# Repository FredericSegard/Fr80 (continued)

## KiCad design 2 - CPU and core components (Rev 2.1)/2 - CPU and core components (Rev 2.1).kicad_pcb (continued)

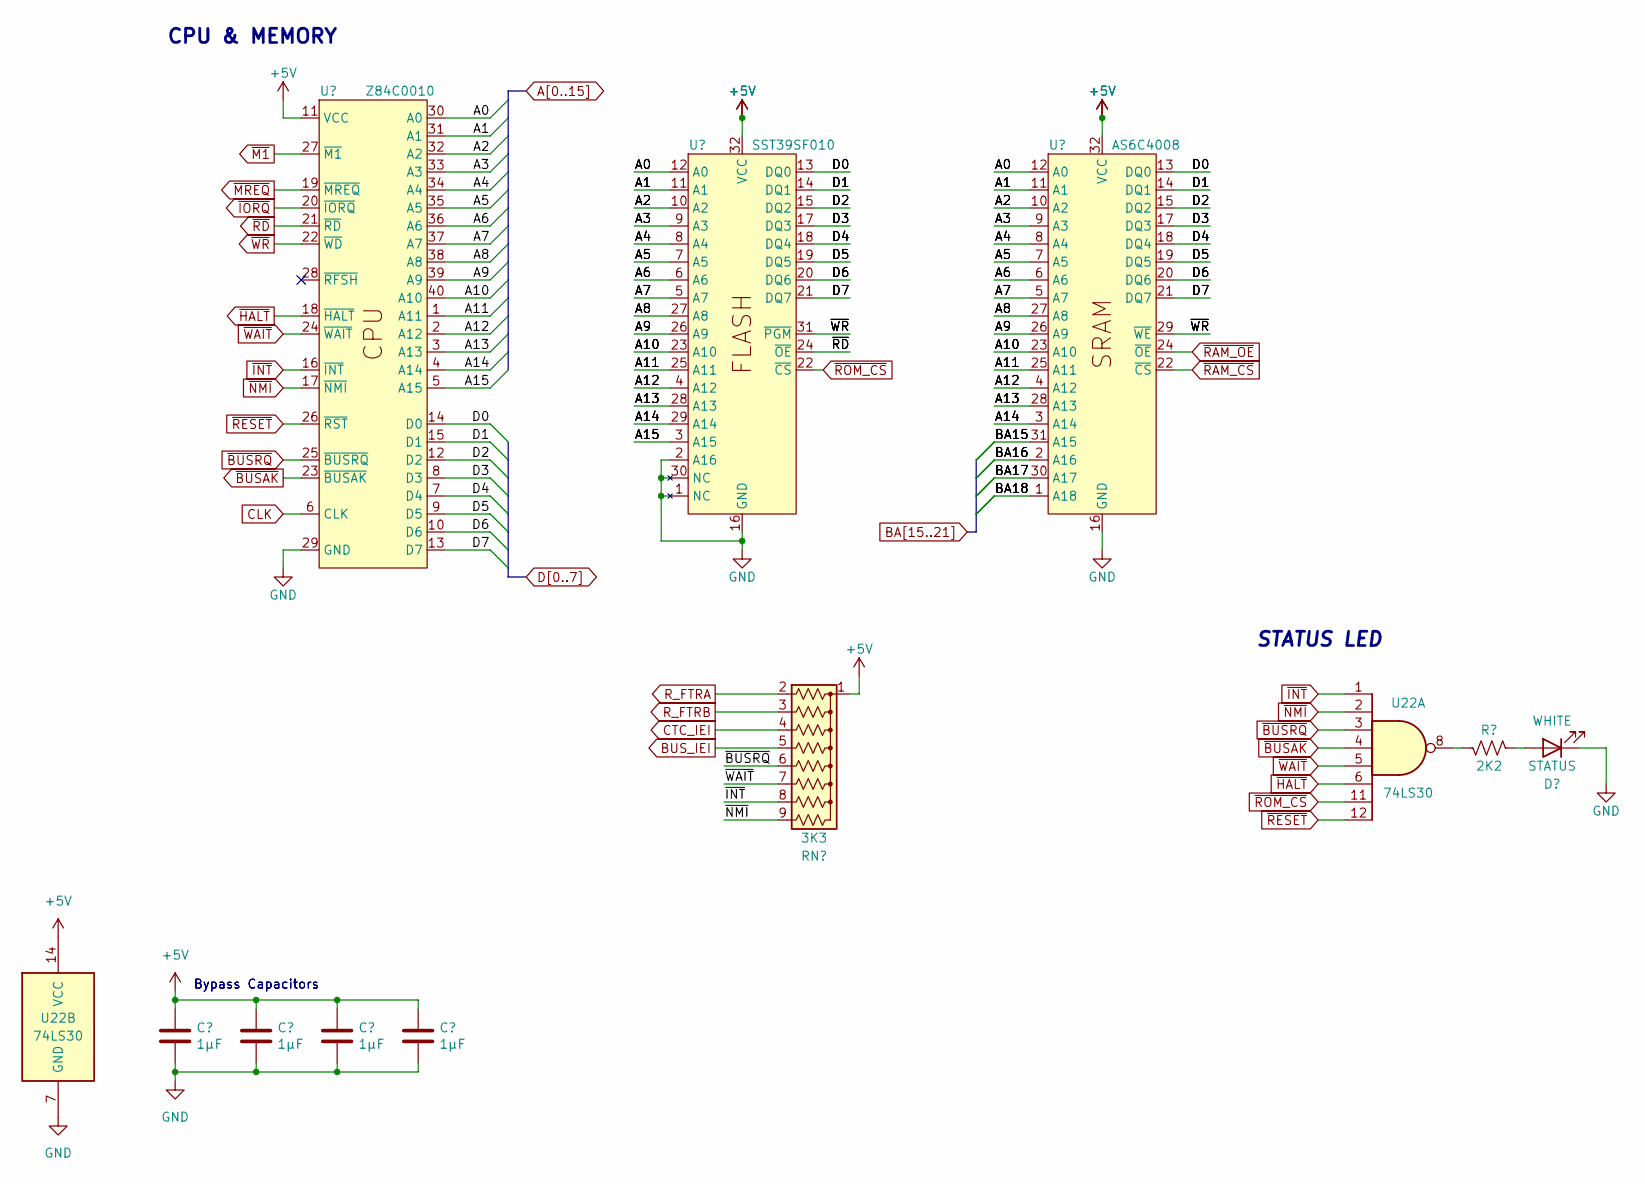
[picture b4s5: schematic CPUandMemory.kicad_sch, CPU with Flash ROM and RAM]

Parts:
C17, C18, C19, C26: 1µF; C_Disc_D3.4mm_W2.1mm_P2.50mm
D1: STATUS; LED_D3.0mm_Horizontal_O1.27mm_Z2.0mm_Clear
R2: 2K2; R_Axial_DIN0207_L6.3mm_D2.5mm_P10.16mm_Horizontal
RN3: 3K3; R_Array_SIP9
U15: Z84C0010; DIP-40_W15.24mm_Socket
U16: SST39SF010; ZIF_Socket-32
U17: AS6C4008; DIP-32_W15.24mm_Socket
U22: 74LS30; DIP-14_W7.62mm_Socket

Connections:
A0: U15.30 (A0), U16.12 (A0), U17.12 (A0); also elsewhere on the board
A1: U15.31 (A1), U16.11 (A1), U17.11 (A1); also elsewhere on the board
A2: U15.32 (A2), U16.10 (A2), U17.10 (A2); also elsewhere on the board
A3: U15.33 (A3), U16.9 (A3), U17.9 (A3); also elsewhere on the board
A4: U15.34 (A4), U16.8 (A4), U17.8 (A4); also elsewhere on the board
A5: U15.35 (A5), U16.7 (A5), U17.7 (A5); also elsewhere on the board
A6: U15.36 (A6), U16.6 (A6), U17.6 (A6); also elsewhere on the board
A7: U15.37 (A7), U16.5 (A7), U17.5 (A7); also elsewhere on the board
A8: U15.38 (A8), U16.27 (A8), U17.27 (A8); also elsewhere on the board
A9: U15.39 (A9), U16.26 (A9), U17.26 (A9); also elsewhere on the board
A10: U15.40 (A10), U16.23 (A10), U17.23 (A10); also elsewhere on the board
A11: U15.1 (A11), U16.25 (A11), U17.25 (A11); also elsewhere on the board
A12: U15.2 (A12), U16.4 (A12), U17.4 (A12); also elsewhere on the board
A13: U15.3 (A13), U16.28 (A13), U17.28 (A13); also elsewhere on the board
A14: U15.4 (A14), U16.29 (A14), U17.3 (A14); also elsewhere on the board
A15: U15.5 (A15), U16.3 (A15); also elsewhere on the board
BA15: U17.31 (A15); also elsewhere on the board
BA16: U17.2 (A16); also elsewhere on the board
BA17: U17.30 (A17); also elsewhere on the board
BA18: U17.1 (A18); also elsewhere on the board
BUS_IEI: RN3.5 (R4); also elsewhere on the board
CLK: U15.6 (CLK); also elsewhere on the board
CTC_IEI: RN3.4 (R3); also elsewhere on the board
D0: U15.14 (D0), U16.13 (DQ0), U17.13 (DQ0); also elsewhere on the board
D1: U15.15 (D1), U16.14 (DQ1), U17.14 (DQ1); also elsewhere on the board
D2: U15.12 (D2), U16.15 (DQ2), U17.15 (DQ2); also elsewhere on the board
D3: U15.8 (D3), U16.17 (DQ3), U17.17 (DQ3); also elsewhere on the board
D4: U15.7 (D4), U16.18 (DQ4), U17.18 (DQ4); also elsewhere on the board
D5: U15.9 (D5), U16.19 (DQ5), U17.19 (DQ5); also elsewhere on the board
D6: U15.10 (D6), U16.20 (DQ6), U17.20 (DQ6); also elsewhere on the board
D7: U15.13 (D7), U16.21 (DQ7), U17.21 (DQ7); also elsewhere on the board
R_FTRB: RN3.3 (R2); also elsewhere on the board
~BUSAK: U15.23 (~BUSAK), U22.4; also elsewhere on the board
~BUSRQ: RN3.6 (R5), U15.25 (~BUSRQ), U22.3; also elsewhere on the board
~HALT: U15.18 (~HALT), U22.6; also elsewhere on the board
~INT: RN3.8 (R7), U15.16 (~INT), U22.1; also elsewhere on the board
~IORQ: U15.20 (~IORQ); also elsewhere on the board
~M1: U15.27 (~M1); also elsewhere on the board
~MREQ: U15.19 (~MREQ); also elsewhere on the board
~NMI: RN3.9 (R8), U15.17 (~NMI), U22.2; also elsewhere on the board
~RAM_CS: U17.22 (~CS); also elsewhere on the board
~RAM_OE: U17.24 (~OE); also elsewhere on the board
~RD: U15.21 (~RD), U16.24 (~OE); also elsewhere on the board
~RESET: U15.26 (~RST), U22.12; also elsewhere on the board
~ROM_CS: U16.22 (~CS), U22.11; also elsewhere on the board
~WAIT: RN3.7 (R6), U15.24 (~WAIT), U22.5; also elsewhere on the board
~WR: U15.22 (~WD), U16.31 (~PGM), U17.29 (~WE); also elsewhere on the board

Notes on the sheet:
STATUS LED
Bypass Capacitors
CPU & MEMORY

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
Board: 2 copper layers, 75 parts (0 on the bottom side), 163 nets, no tracks yet.

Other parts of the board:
D9: STATUS; LED_D3.0mm_Horizontal_O1.27mm_Z2.0mm_Clear
R7: 2K2; R_Axial_DIN0207_L6.3mm_D2.5mm_P10.16mm_Horizontal

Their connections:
unnamed: D9.2 (A), R7.1

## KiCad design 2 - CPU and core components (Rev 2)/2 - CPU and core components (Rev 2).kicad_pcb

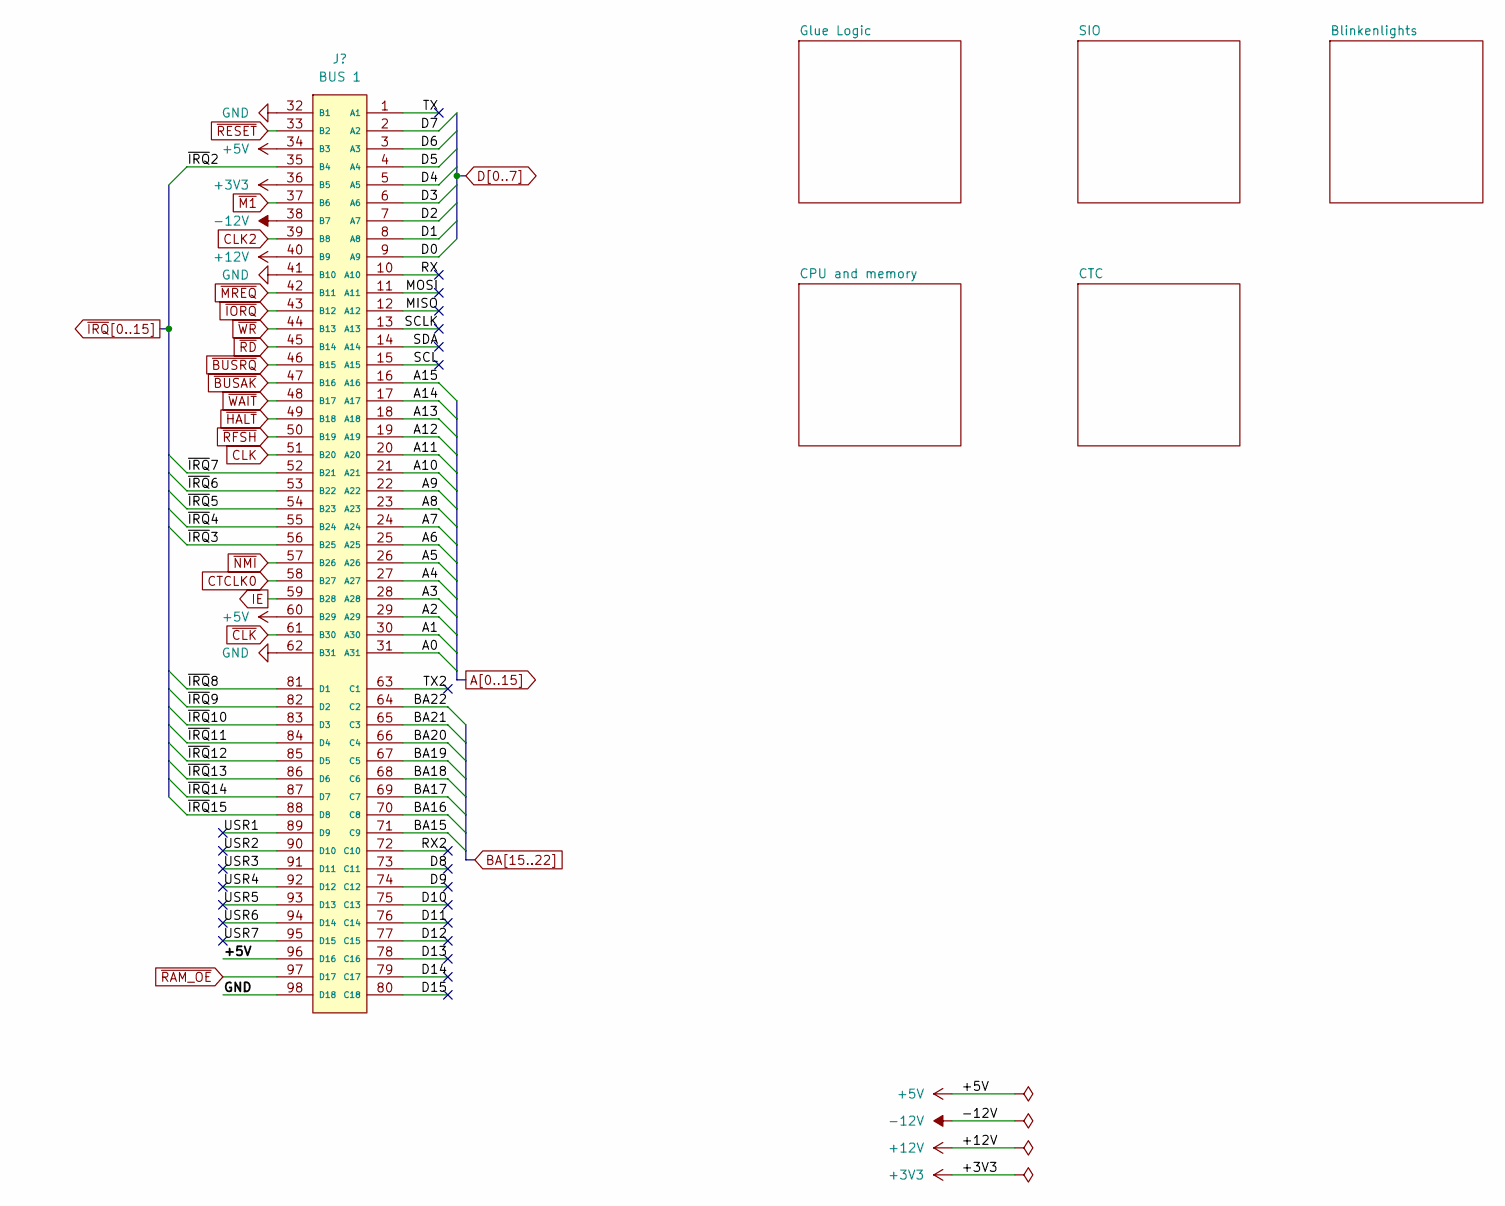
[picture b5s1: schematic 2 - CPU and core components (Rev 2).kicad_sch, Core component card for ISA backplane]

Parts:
J2: BUS 1; BUS_AT v2

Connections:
+3V3: J2.36 (B5)
+5V: J2.34 (B3), J2.60 (B29), J2.96 (D16); also elsewhere on the board
+12V: J2.40 (B9)
-12V: J2.38 (B7)
/D8: J2.73 (C11)
/D9: J2.74 (C12)
/D10: J2.75 (C13)
/D11: J2.76 (C14)
/D12: J2.77 (C15)
/D13: J2.78 (C16)
/D14: J2.79 (C17)
/D15: J2.80 (C18)
/MISO: J2.12 (A12)
/MOSI: J2.11 (A11)
/RX: J2.10 (A10)
/RX2: J2.72 (C10)
/SCL: J2.15 (A15)
/SCLK: J2.13 (A13)
/SDA: J2.14 (A14)
/TX: J2.1 (A1)
/TX2: J2.63 (C1)
/USR1: J2.89 (D9)
/USR2: J2.90 (D10)
/USR3: J2.91 (D11)
/USR4: J2.92 (D12)
/USR5: J2.93 (D13)
/USR6: J2.94 (D14)
/USR7: J2.95 (D15)
A0: J2.31 (A31); also elsewhere on the board
A1: J2.30 (A30); also elsewhere on the board
A2: J2.29 (A29); also elsewhere on the board
A3: J2.28 (A28); also elsewhere on the board
A4: J2.27 (A27); also elsewhere on the board
A5: J2.26 (A26); also elsewhere on the board
A6: J2.25 (A25); also elsewhere on the board
A7: J2.24 (A24); also elsewhere on the board
A8: J2.23 (A23); also elsewhere on the board
A9: J2.22 (A22); also elsewhere on the board
A10: J2.21 (A21); also elsewhere on the board
A11: J2.20 (A20); also elsewhere on the board
A12: J2.19 (A19); also elsewhere on the board
A13: J2.18 (A18); also elsewhere on the board
A14: J2.17 (A17); also elsewhere on the board
A15: J2.16 (A16); also elsewhere on the board
BA15: J2.71 (C9); also elsewhere on the board
BA16: J2.70 (C8); also elsewhere on the board
BA17: J2.69 (C7); also elsewhere on the board
BA18: J2.68 (C6); also elsewhere on the board
BA19: J2.67 (C5); also elsewhere on the board
BA20: J2.66 (C4); also elsewhere on the board
BA21: J2.65 (C3); also elsewhere on the board
BA22: J2.64 (C2); also elsewhere on the board
CLK: J2.51 (B20); also elsewhere on the board
CLK2: J2.39 (B8); also elsewhere on the board
CTCLK0: J2.58 (B27); also elsewhere on the board
D0: J2.9 (A9); also elsewhere on the board
D1: J2.8 (A8); also elsewhere on the board
D2: J2.7 (A7); also elsewhere on the board
D3: J2.6 (A6); also elsewhere on the board
D4: J2.5 (A5); also elsewhere on the board
D5: J2.4 (A4); also elsewhere on the board
D6: J2.3 (A3); also elsewhere on the board
D7: J2.2 (A2); also elsewhere on the board
GND: J2.32 (B1), J2.41 (B10), J2.62 (B31), J2.98 (D18); also elsewhere on the board
IE: J2.59 (B28); also elsewhere on the board
~BUSAK: J2.47 (B16); also elsewhere on the board
~BUSRQ: J2.46 (B15); also elsewhere on the board
~CLK: J2.61 (B30); also elsewhere on the board
~HALT: J2.49 (B18); also elsewhere on the board
~IORQ: J2.43 (B12); also elsewhere on the board
~IRQ2: J2.35 (B4); also elsewhere on the board
~IRQ3: J2.56 (B25); also elsewhere on the board
~IRQ4: J2.55 (B24); also elsewhere on the board
~IRQ5: J2.54 (B23); also elsewhere on the board
~IRQ6: J2.53 (B22); also elsewhere on the board
~IRQ7: J2.52 (B21); also elsewhere on the board
~IRQ8: J2.81 (D1); also elsewhere on the board
~IRQ9: J2.82 (D2); also elsewhere on the board
~IRQ10: J2.83 (D3); also elsewhere on the board
~IRQ11: J2.84 (D4); also elsewhere on the board
~IRQ12: J2.85 (D5); also elsewhere on the board
~IRQ13: J2.86 (D6); also elsewhere on the board
~IRQ14: J2.87 (D7); also elsewhere on the board
~IRQ15: J2.88 (D8); also elsewhere on the board
~M1: J2.37 (B6); also elsewhere on the board
~MREQ: J2.42 (B11); also elsewhere on the board
~NMI: J2.57 (B26); also elsewhere on the board
~RAM_OE: J2.97 (D17); also elsewhere on the board
~RD: J2.45 (B14); also elsewhere on the board
~RESET: J2.33 (B2); also elsewhere on the board
~RFSH: J2.50 (B19); also elsewhere on the board
~WAIT: J2.48 (B17); also elsewhere on the board
~WR: J2.44 (B13); also elsewhere on the board

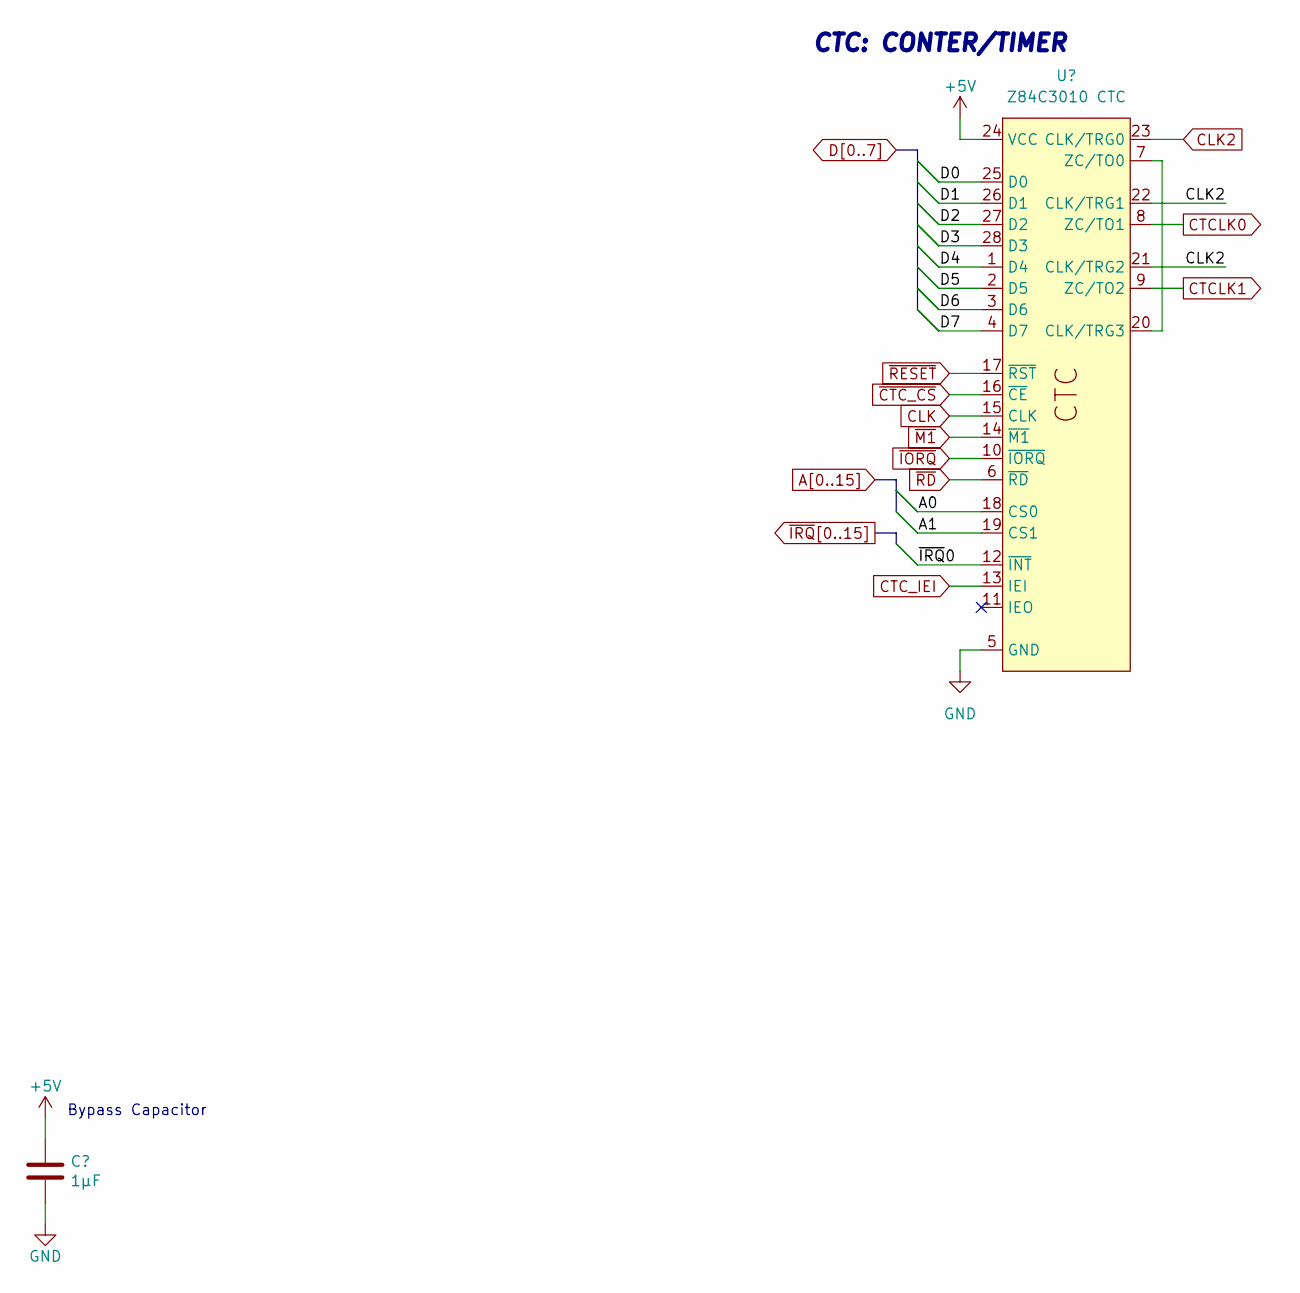
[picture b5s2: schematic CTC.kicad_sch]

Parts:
C14: 1µF; C_Disc_D3.4mm_W2.1mm_P2.50mm
U13: Z84C3010 CTC; DIP-28_W15.24mm_Socket

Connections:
+5V: C14.1, U13.24 (VCC); also elsewhere on the board
A0: U13.18 (CS0); also elsewhere on the board
A1: U13.19 (CS1); also elsewhere on the board
CLK: U13.15 (CLK); also elsewhere on the board
CLK2: U13.21 (CLK/TRG2), U13.22 (CLK/TRG1), U13.23 (CLK/TRG0); also elsewhere on the board
CTCLK0: U13.8 (ZC/TO1); also elsewhere on the board
CTCLK1: U13.9 (ZC/TO2); also elsewhere on the board
CTC_IEI: U13.13 (IEI); also elsewhere on the board
D0: U13.25 (D0); also elsewhere on the board
D1: U13.26 (D1); also elsewhere on the board
D2: U13.27 (D2); also elsewhere on the board
D3: U13.28 (D3); also elsewhere on the board
D4: U13.1 (D4); also elsewhere on the board
D5: U13.2 (D5); also elsewhere on the board
D6: U13.3 (D6); also elsewhere on the board
D7: U13.4 (D7); also elsewhere on the board
GND: C14.2, U13.5 (GND); also elsewhere on the board
unnamed: U13.7 (ZC/TO0), U13.20 (CLK/TRG3)
~CTC_CS: U13.16 (~CE); also elsewhere on the board
~IORQ: U13.10 (~IORQ); also elsewhere on the board
~IRQ0: U13.12 (~INT); also elsewhere on the board
~M1: U13.14 (~M1); also elsewhere on the board
~RD: U13.6 (~RD); also elsewhere on the board
~RESET: U13.17 (~RST); also elsewhere on the board

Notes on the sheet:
CTC: CONTER/TIMER
Bypass Capacitor

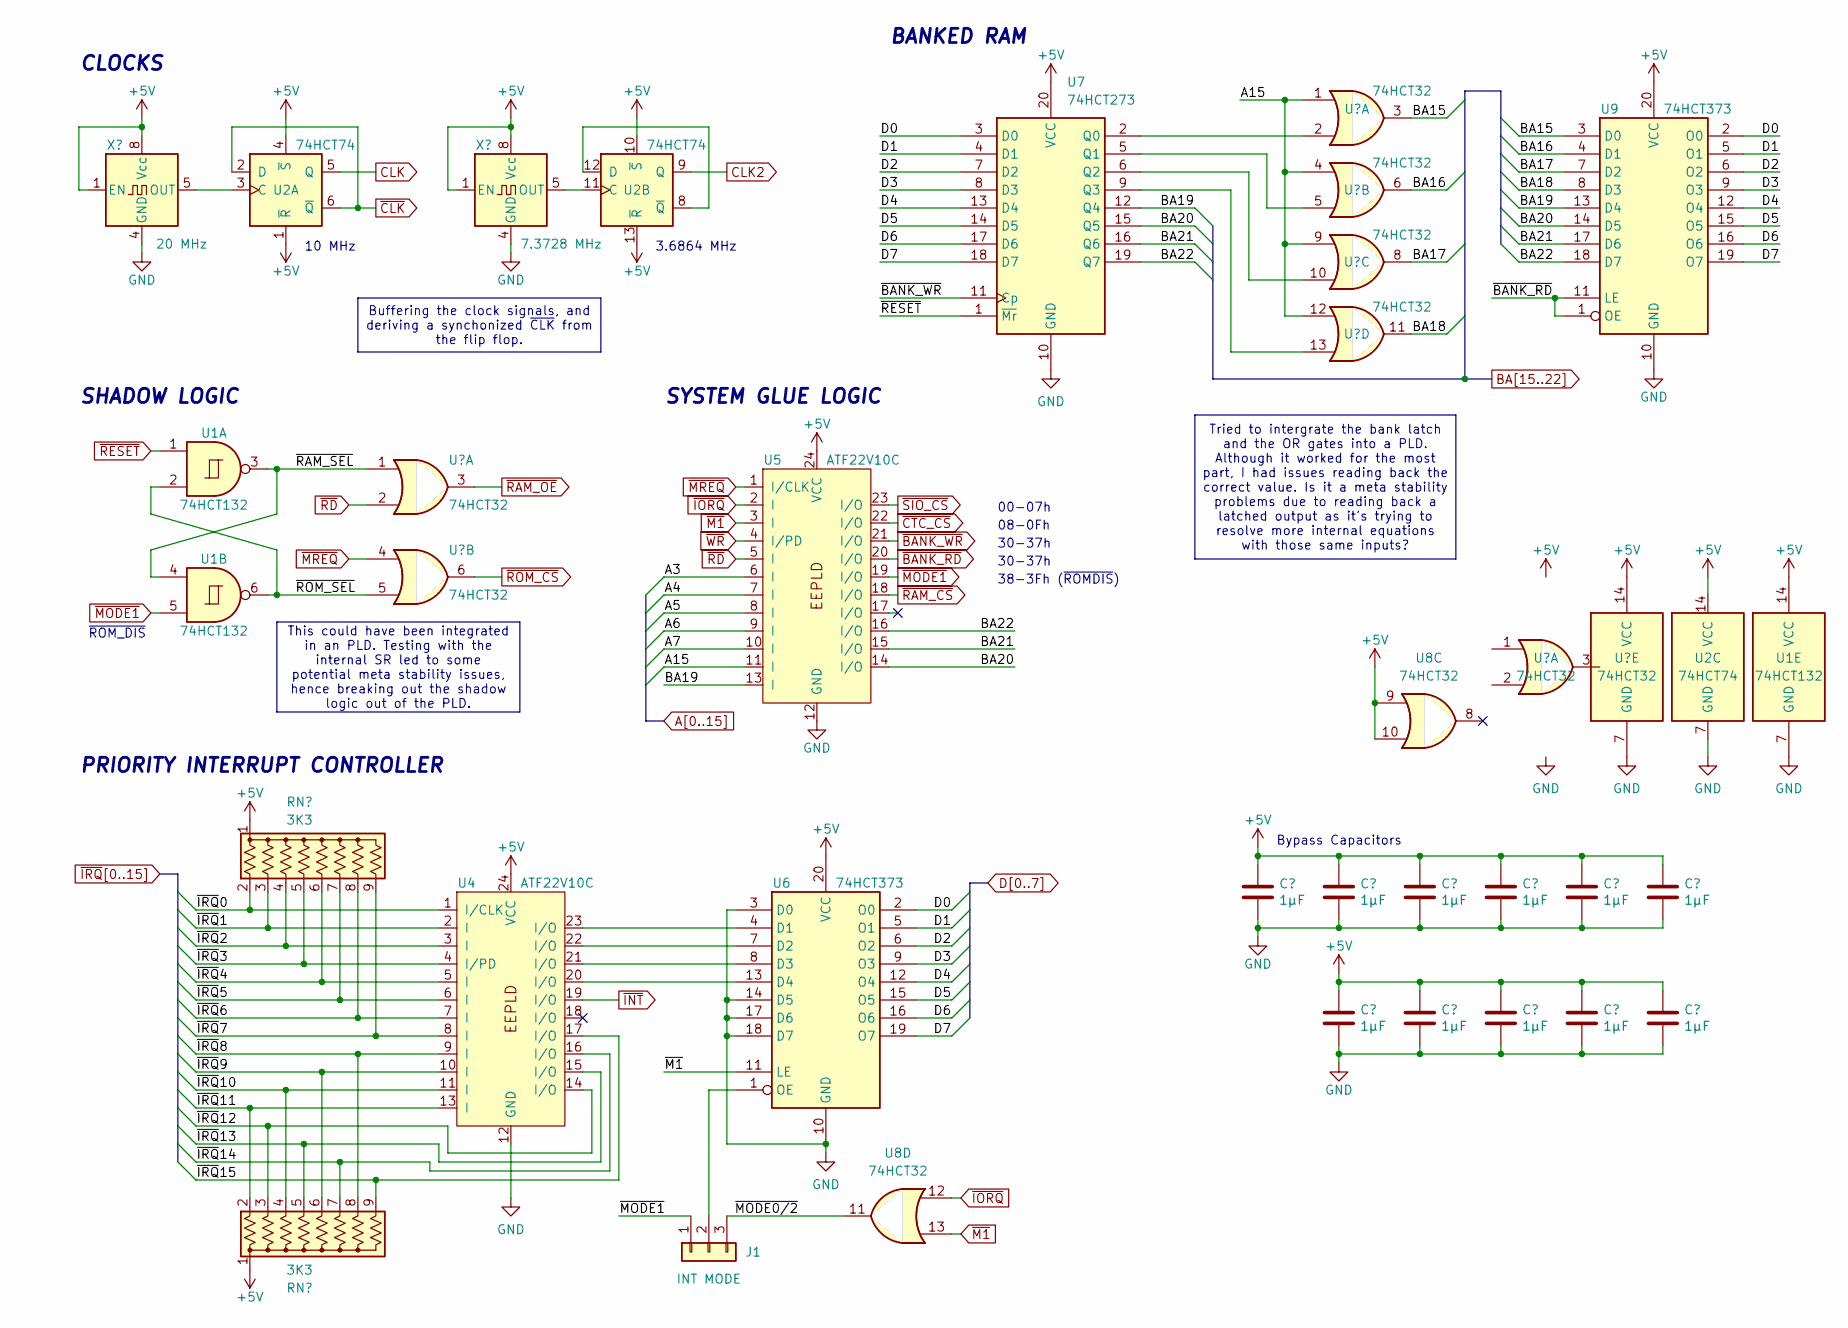
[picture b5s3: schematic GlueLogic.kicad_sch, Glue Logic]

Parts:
C1, C2, C3, C4, C7: 1µF; C_Disc_D3.0mm_W1.6mm_P2.50mm
C5, C6, C8, C9, C20, C21: 1µF; C_Disc_D3.0mm_W2.0mm_P2.50mm
J1: INT MODE; PinHeader_1x03_P2.54mm_Vertical
RN1, RN2: 3K3; R_Array_SIP9
U1: 74HCT132; DIP-14_W7.62mm_Socket
U2: 74HCT74; DIP-14_W7.62mm_Socket
U3, U8: 74HCT32; DIP-14_W7.62mm_Socket
U4, U5: ATF22V10C; DIP-24_W7.62mm_Socket
U6, U9: 74HCT373; DIP-20_W7.62mm_Socket
U7: 74HCT273; DIP-20_W7.62mm_Socket
X1: 20 MHz; DIP-8-4_W7.62mm_Oscillator_Socket
X2: 7.3728 MHz; DIP-8-4_W7.62mm_Oscillator_Socket

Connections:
+5V: C1.1, C2.1, C3.1, C4.1, C5.1, C6.1, C7.1, C8.1, C9.1, C20.1, C21.1, RN1.1 (common), RN2.1 (common), U1.14 (VCC), U2.1 (~R), U2.4 (~S), U2.10 (~S), U2.13 (~R), U2.14 (VCC), U3.14 (VCC), U4.24 (VCC), U5.24 (VCC), U6.20 (VCC), U7.20 (VCC), U8.9, U8.10, U8.14 (VCC), U9.20 (VCC), X1.1 (EN), X1.8 (Vcc), X2.1 (EN), X2.8 (Vcc); also elsewhere on the board
/Glue Logic/~MODE0/2: J1.3, U8.11
/Glue Logic/~RAM_SEL: U1.3, U1.4, U3.1
/Glue Logic/~ROM_SEL: U1.2, U1.6, U3.5
A3: U5.6 (I); also elsewhere on the board
A4: U5.7 (I); also elsewhere on the board
A5: U5.8 (I); also elsewhere on the board
A6: U5.9 (I); also elsewhere on the board
A7: U5.10 (I); also elsewhere on the board
A15: U3.9, U3.12, U5.11 (I), U8.1, U8.4; also elsewhere on the board
BA15: U8.3, U9.3 (D0); also elsewhere on the board
BA16: U8.6, U9.4 (D1); also elsewhere on the board
BA17: U3.8, U9.7 (D2); also elsewhere on the board
BA18: U3.11, U9.8 (D3); also elsewhere on the board
BA19: U5.13 (I), U7.12 (Q4), U9.13 (D4); also elsewhere on the board
BA20: U5.14 (I/O), U7.15 (Q5), U9.14 (D5); also elsewhere on the board
BA21: U5.15 (I/O), U7.16 (Q6), U9.17 (D6); also elsewhere on the board
BA22: U5.16 (I/O), U7.19 (Q7), U9.18 (D7); also elsewhere on the board
CLK: U2.5 (Q); also elsewhere on the board
CLK2: U2.9 (Q); also elsewhere on the board
D0: U6.2 (O0), U7.3 (D0), U9.2 (O0); also elsewhere on the board
D1: U6.5 (O1), U7.4 (D1), U9.5 (O1); also elsewhere on the board
D2: U6.6 (O2), U7.7 (D2), U9.6 (O2); also elsewhere on the board
D3: U6.9 (O3), U7.8 (D3), U9.9 (O3); also elsewhere on the board
D4: U6.12 (O4), U7.13 (D4), U9.12 (O4); also elsewhere on the board
D5: U6.15 (O5), U7.14 (D5), U9.15 (O5); also elsewhere on the board
D6: U6.16 (O6), U7.17 (D6), U9.16 (O6); also elsewhere on the board
D7: U6.19 (O7), U7.18 (D7), U9.19 (O7); also elsewhere on the board
GND: C1.2, C2.2, C3.2, C4.2, C5.2, C6.2, C7.2, C8.2, C9.2, C20.2, C21.2, U1.7 (GND), U2.7 (GND), U3.7 (GND), U4.12 (GND), U5.12 (GND), U6.3 (D0), U6.10 (GND), U6.14 (D5), U6.17 (D6), U6.18 (D7), U7.10 (GND), U8.7 (GND), U9.10 (GND), X1.4 (GND), X2.4 (GND); also elsewhere on the board
unnamed: J1.2, U6.1 (OE)
unnamed: U2.3 (C), X1.5 (OUT)
unnamed: U2.11 (C), X2.5 (OUT)
unnamed: U2.8 (~Q), U2.12 (D)
unnamed: U4.23 (I/O), U6.4 (D1)
unnamed: U4.22 (I/O), U6.7 (D2)
unnamed: U4.21 (I/O), U6.8 (D3)
unnamed: U4.20 (I/O), U6.13 (D4)
unnamed: U7.2 (Q0), U8.2
unnamed: U7.5 (Q1), U8.5
unnamed: U3.10, U7.6 (Q2)
unnamed: U3.13, U7.9 (Q3)
~BANK_RD: U5.20 (I/O), U9.1 (OE), U9.11 (LE)
~BANK_WR: U5.21 (I/O), U7.11 (Cp)
~CLK: U2.2 (D), U2.6 (~Q); also elsewhere on the board
~CTC_CS: U5.22 (I/O); also elsewhere on the board
~INT: U4.19 (I/O); also elsewhere on the board
~IORQ: U5.2 (I), U8.12; also elsewhere on the board
~IRQ0: RN1.2 (R1), U4.1 (I/CLK); also elsewhere on the board
~IRQ1: RN1.3 (R2), U4.2 (I); also elsewhere on the board
~IRQ2: RN1.4 (R3), U4.3 (I); also elsewhere on the board
~IRQ3: RN1.5 (R4), U4.4 (I/PD); also elsewhere on the board
~IRQ4: RN1.6 (R5), U4.5 (I); also elsewhere on the board
~IRQ5: RN1.7 (R6), U4.6 (I); also elsewhere on the board
~IRQ6: RN1.8 (R7), U4.7 (I); also elsewhere on the board
~IRQ7: RN1.9 (R8), U4.8 (I); also elsewhere on the board
~IRQ8: RN2.8 (R7), U4.9 (I); also elsewhere on the board
~IRQ9: RN2.6 (R5), U4.10 (I); also elsewhere on the board
~IRQ10: RN2.4 (R3), U4.11 (I); also elsewhere on the board
~IRQ11: RN2.2 (R1), U4.13 (I); also elsewhere on the board
~IRQ12: RN2.3 (R2), U4.14 (I/O); also elsewhere on the board
~IRQ13: RN2.5 (R4), U4.15 (I/O); also elsewhere on the board
~IRQ14: RN2.7 (R6), U4.16 (I/O); also elsewhere on the board
~IRQ15: RN2.9 (R8), U4.17 (I/O); also elsewhere on the board
~M1: U5.3 (I), U6.11 (LE), U8.13; also elsewhere on the board
~MODE1: J1.1, U1.5, U5.19 (I/O)
~MREQ: U3.4, U5.1 (I/CLK); also elsewhere on the board
~RAM_CS: U5.18 (I/O); also elsewhere on the board
~RAM_OE: U3.3; also elsewhere on the board
~RD: U3.2, U5.5 (I); also elsewhere on the board
~RESET: U1.1, U7.1 (~Mr); also elsewhere on the board
~ROM_CS: U3.6; also elsewhere on the board
~SIO_CS: U5.23 (I/O); also elsewhere on the board
~WR: U5.4 (I/PD); also elsewhere on the board

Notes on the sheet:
Buffering the clock signals, and deriving a synchonized ~{CLK} from the flip flop.
Tried to intergrate the bank latch and the OR gates into a PLD. Although it worked for the most part, I had issues reading back the correct value. Is it a meta stability problems due to reading back a latched output as it's trying to resolve more internal equations with those same inputs?
This could have been integrated in an PLD. Testing with the internal SR led to some potential meta stability issues, hence breaking out the shadow logic out of the PLD.
Bypass Capacitors
38-3Fh (~{ROMDIS})
08-0Fh
30-37h
BANKED RAM
~{ROM_DIS}
10 MHz
00-07h
PRIORITY INTERRUPT CONTROLLER
CLOCKS
3.6864 MHz
SHADOW LOGIC
SYSTEM GLUE LOGIC

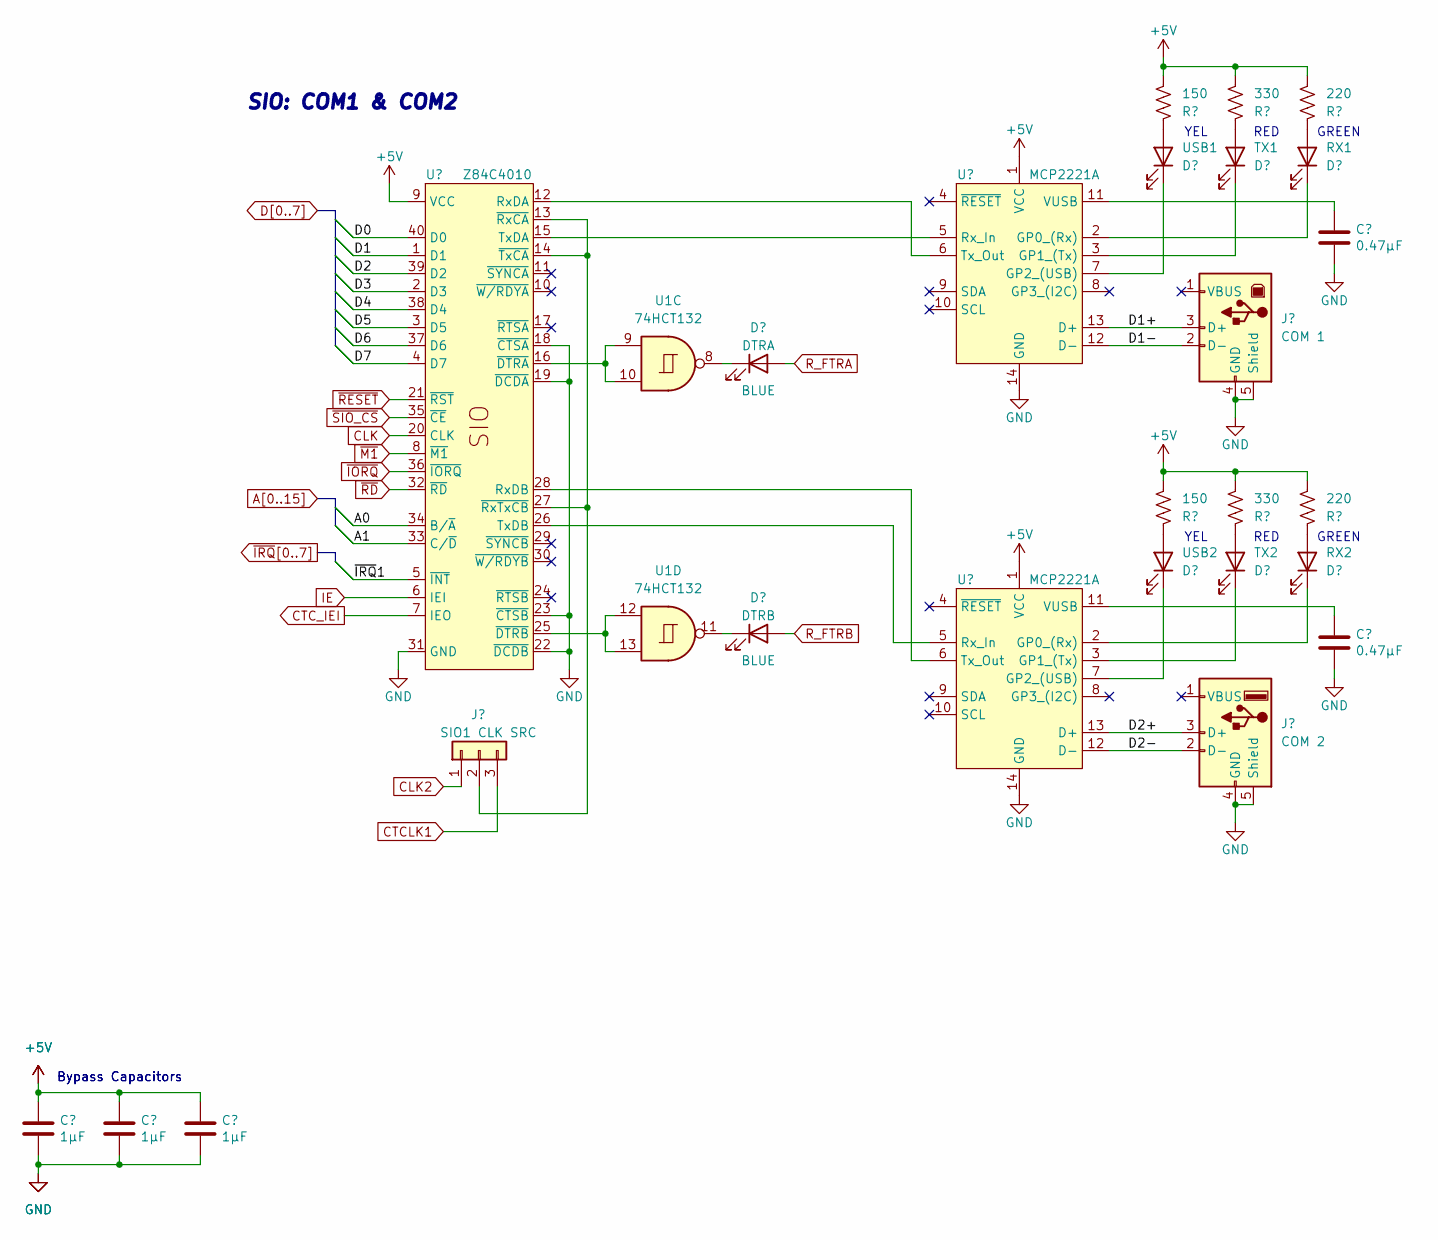
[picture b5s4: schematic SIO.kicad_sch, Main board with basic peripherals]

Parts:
C15, C16, C17: 1µF; C_Disc_D3.4mm_W2.1mm_P2.50mm
C18, C19: 0.47µF; C_Disc_D3.4mm_W2.1mm_P2.50mm
D1: DTRA; LED_D3.0mm_Horizontal_O1.27mm_Z2.0mm_Clear
D2: DTRB; LED_D3.0mm_Horizontal_O1.27mm_Z2.0mm_Clear
D3: USB1; LED_D3.0mm_Horizontal_O1.27mm_Z2.0mm_Clear
D4: USB2; LED_D3.0mm_Horizontal_O1.27mm_Z2.0mm_Clear
D5: TX1; LED_D3.0mm_Horizontal_O1.27mm_Z2.0mm_Clear
D6: TX2; LED_D3.0mm_Horizontal_O1.27mm_Z2.0mm_Clear
D7: RX1; LED_D3.0mm_Horizontal_O1.27mm_Z2.0mm_Clear
D8: RX2; LED_D3.0mm_Horizontal_O1.27mm_Z2.0mm_Clear
J3: SIO1 CLK SRC; PinHeader_1x03_P2.54mm_Vertical
J4: COM 1; USB_B_Lumberg_2411_02_Horizontal
J5: COM 2; USB_A_Stewart_SS-52100-001_Horizontal
R1, R2: 150; R_Axial_DIN0207_L6.3mm_D2.5mm_P10.16mm_Horizontal
R3, R4: 330; R_Axial_DIN0207_L6.3mm_D2.5mm_P10.16mm_Horizontal
R5, R6: 220; R_Axial_DIN0207_L6.3mm_D2.5mm_P10.16mm_Horizontal
U1: 74HCT132; DIP-14_W7.62mm_Socket
U14: Z84C4010; DIP-40_W15.24mm_Socket
U15, U16: MCP2221A; DIP-14_W7.62mm_Socket

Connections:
+5V: C15.1, C16.1, C17.1, R1.2, R2.2, R3.2, R4.2, R5.2, R6.2, U14.9 (VCC), U15.1 (VCC), U16.1 (VCC); also elsewhere on the board
/SIO/D1+: J4.3 (D+), U15.13 (D+)
/SIO/D1-: J4.2 (D-), U15.12 (D-)
/SIO/D2+: J5.3 (D+), U16.13 (D+)
/SIO/D2-: J5.2 (D-), U16.12 (D-)
A0: U14.34 (B/~A); also elsewhere on the board
A1: U14.33 (C/~D); also elsewhere on the board
CLK: U14.20 (CLK); also elsewhere on the board
CLK2: J3.1; also elsewhere on the board
CTCLK1: J3.3; also elsewhere on the board
CTC_IEI: U14.7 (IEO); also elsewhere on the board
D0: U14.40 (D0); also elsewhere on the board
D1: U14.1 (D1); also elsewhere on the board
D2: U14.39 (D2); also elsewhere on the board
D3: U14.2 (D3); also elsewhere on the board
D4: U14.38 (D4); also elsewhere on the board
D5: U14.3 (D5); also elsewhere on the board
D6: U14.37 (D6); also elsewhere on the board
D7: U14.4 (D7); also elsewhere on the board
GND: C15.2, C16.2, C17.2, C18.2, C19.2, J4.4 (GND), J4.5 (Shield), J5.4 (GND), J5.5 (Shield), U14.18 (~CTSA), U14.19 (~DCDA), U14.22 (~DCDB), U14.23 (~CTSB), U14.31 (GND), U15.14 (GND), U16.14 (GND); also elsewhere on the board
IE: U14.6 (IEI); also elsewhere on the board
unnamed: D1.1 (K), U1.8
unnamed: D2.1 (K), U1.11
unnamed: D3.2 (A), R1.1
unnamed: D3.1 (K), U15.7 (GP2_(USB))
unnamed: D4.2 (A), R2.1
unnamed: D4.1 (K), U16.7 (GP2_(USB))
unnamed: D5.2 (A), R3.1
unnamed: D5.1 (K), U15.3 (GP1_(Tx))
unnamed: D6.2 (A), R4.1
unnamed: D6.1 (K), U16.3 (GP1_(Tx))
unnamed: D7.2 (A), R5.1
unnamed: D7.1 (K), U15.2 (GP0_(Rx))
unnamed: D8.2 (A), R6.1
unnamed: D8.1 (K), U16.2 (GP0_(Rx))
unnamed: J3.2, U14.13 (~RxCA), U14.14 (~TxCA), U14.27 (~RxTxCB)
unnamed: U14.12 (RxDA), U15.6 (Tx_Out)
unnamed: U14.28 (RxDB), U16.6 (Tx_Out)
unnamed: U14.15 (TxDA), U15.5 (Rx_In)
unnamed: U14.26 (TxDB), U16.5 (Rx_In)
unnamed: U1.9, U1.10, U14.16 (~DTRA)
unnamed: U1.12, U1.13, U14.25 (~DTRB)
unnamed: C18.1, U15.11 (VUSB)
unnamed: C19.1, U16.11 (VUSB)
R_FTRA: D1.2 (A); also elsewhere on the board
R_FTRB: D2.2 (A); also elsewhere on the board
~IORQ: U14.36 (~IORQ); also elsewhere on the board
~IRQ1: U14.5 (~INT); also elsewhere on the board
~M1: U14.8 (~M1); also elsewhere on the board
~RD: U14.32 (~RD); also elsewhere on the board
~RESET: U14.21 (~RST); also elsewhere on the board
~SIO_CS: U14.35 (~CE); also elsewhere on the board

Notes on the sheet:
RED
GREEN
YEL
SIO: COM1 & COM2
Bypass Capacitors
